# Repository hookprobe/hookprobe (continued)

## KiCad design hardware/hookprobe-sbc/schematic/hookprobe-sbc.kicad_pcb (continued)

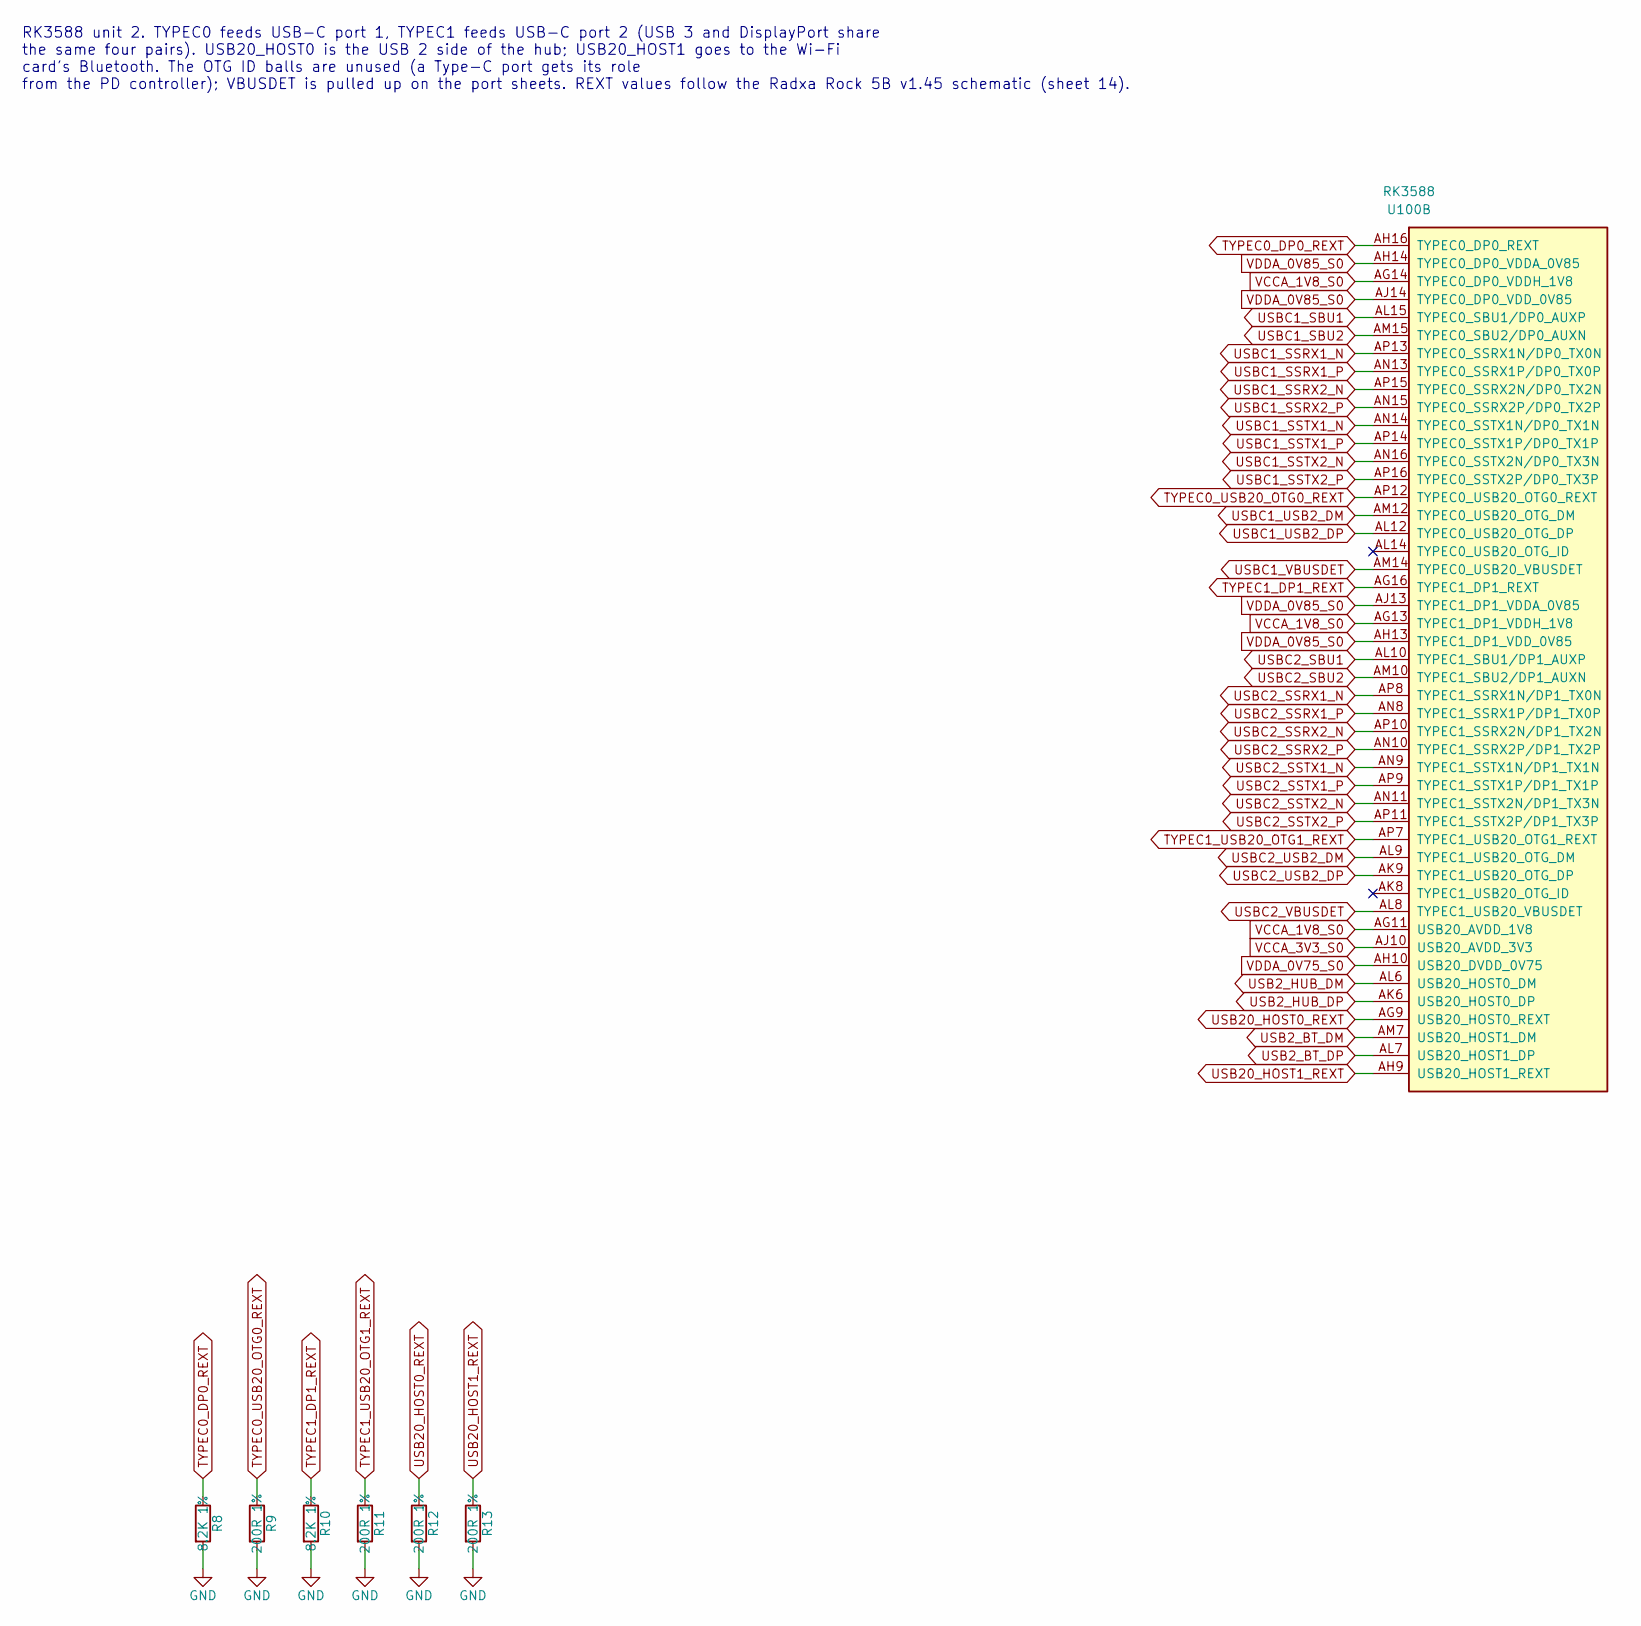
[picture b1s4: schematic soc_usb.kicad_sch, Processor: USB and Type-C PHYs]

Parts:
R8, R10: 8.2K 1%; R_0402_1005Metric
R9, R11, R12, R13: 200R 1%; R_0402_1005Metric
U100: RK3588; FCBGA-1088_L23.0-W23.0-P0.65-TL_RK3588

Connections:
GND: R8.2, R9.2, R10.2, R11.2, R12.2, R13.2; also elsewhere on the board
TYPEC0_DP0_REXT: R8.1, U100.AH16 (TYPEC0_DP0_REXT)
TYPEC0_USB20_OTG0_REXT: R9.1, U100.AP12 (TYPEC0_USB20_OTG0_REXT)
TYPEC1_DP1_REXT: R10.1, U100.AG16 (TYPEC1_DP1_REXT)
TYPEC1_USB20_OTG1_REXT: R11.1, U100.AP7 (TYPEC1_USB20_OTG1_REXT)
USB2_BT_DM: U100.AM7 (USB20_HOST1_DM); also elsewhere on the board
USB2_BT_DP: U100.AL7 (USB20_HOST1_DP); also elsewhere on the board
USB2_HUB_DM: U100.AL6 (USB20_HOST0_DM); also elsewhere on the board
USB2_HUB_DP: U100.AK6 (USB20_HOST0_DP); also elsewhere on the board
USB20_HOST0_REXT: R12.1, U100.AG9 (USB20_HOST0_REXT)
USB20_HOST1_REXT: R13.1, U100.AH9 (USB20_HOST1_REXT)
USBC1_SBU1: U100.AL15 (TYPEC0_SBU1/DP0_AUXP); also elsewhere on the board
USBC1_SBU2: U100.AM15 (TYPEC0_SBU2/DP0_AUXN); also elsewhere on the board
USBC1_SSRX1_N: U100.AP13 (TYPEC0_SSRX1N/DP0_TX0N); also elsewhere on the board
USBC1_SSRX1_P: U100.AN13 (TYPEC0_SSRX1P/DP0_TX0P); also elsewhere on the board
USBC1_SSRX2_N: U100.AP15 (TYPEC0_SSRX2N/DP0_TX2N); also elsewhere on the board
USBC1_SSRX2_P: U100.AN15 (TYPEC0_SSRX2P/DP0_TX2P); also elsewhere on the board
USBC1_SSTX1_N: U100.AN14 (TYPEC0_SSTX1N/DP0_TX1N); also elsewhere on the board
USBC1_SSTX1_P: U100.AP14 (TYPEC0_SSTX1P/DP0_TX1P); also elsewhere on the board
USBC1_SSTX2_N: U100.AN16 (TYPEC0_SSTX2N/DP0_TX3N); also elsewhere on the board
USBC1_SSTX2_P: U100.AP16 (TYPEC0_SSTX2P/DP0_TX3P); also elsewhere on the board
USBC1_USB2_DM: U100.AM12 (TYPEC0_USB20_OTG_DM); also elsewhere on the board
USBC1_USB2_DP: U100.AL12 (TYPEC0_USB20_OTG_DP); also elsewhere on the board
USBC1_VBUSDET: U100.AM14 (TYPEC0_USB20_VBUSDET); also elsewhere on the board
USBC2_SBU1: U100.AL10 (TYPEC1_SBU1/DP1_AUXP); also elsewhere on the board
USBC2_SBU2: U100.AM10 (TYPEC1_SBU2/DP1_AUXN); also elsewhere on the board
USBC2_SSRX1_N: U100.AP8 (TYPEC1_SSRX1N/DP1_TX0N); also elsewhere on the board
USBC2_SSRX1_P: U100.AN8 (TYPEC1_SSRX1P/DP1_TX0P); also elsewhere on the board
USBC2_SSRX2_N: U100.AP10 (TYPEC1_SSRX2N/DP1_TX2N); also elsewhere on the board
USBC2_SSRX2_P: U100.AN10 (TYPEC1_SSRX2P/DP1_TX2P); also elsewhere on the board
USBC2_SSTX1_N: U100.AN9 (TYPEC1_SSTX1N/DP1_TX1N); also elsewhere on the board
USBC2_SSTX1_P: U100.AP9 (TYPEC1_SSTX1P/DP1_TX1P); also elsewhere on the board
USBC2_SSTX2_N: U100.AN11 (TYPEC1_SSTX2N/DP1_TX3N); also elsewhere on the board
USBC2_SSTX2_P: U100.AP11 (TYPEC1_SSTX2P/DP1_TX3P); also elsewhere on the board
USBC2_USB2_DM: U100.AL9 (TYPEC1_USB20_OTG_DM); also elsewhere on the board
USBC2_USB2_DP: U100.AK9 (TYPEC1_USB20_OTG_DP); also elsewhere on the board
USBC2_VBUSDET: U100.AL8 (TYPEC1_USB20_VBUSDET); also elsewhere on the board
VCCA_1V8_S0: U100.AG11 (USB20_AVDD_1V8), U100.AG13 (TYPEC1_DP1_VDDH_1V8), U100.AG14 (TYPEC0_DP0_VDDH_1V8); also elsewhere on the board
VCCA_3V3_S0: U100.AJ10 (USB20_AVDD_3V3); also elsewhere on the board
VDDA_0V75_S0: U100.AH10 (USB20_DVDD_0V75); also elsewhere on the board
VDDA_0V85_S0: U100.AH13 (TYPEC1_DP1_VDD_0V85), U100.AH14 (TYPEC0_DP0_VDDA_0V85), U100.AJ13 (TYPEC1_DP1_VDDA_0V85), U100.AJ14 (TYPEC0_DP0_VDD_0V85); also elsewhere on the board

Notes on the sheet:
RK3588 unit 2. TYPEC0 feeds USB-C port 1, TYPEC1 feeds USB-C port 2 (USB 3 and DisplayPort share the same four pairs). USB20_HOST0 is the USB 2 side of the hub; USB20_HOST1 goes to the Wi-Fi card's Bluetooth. The OTG ID balls are unused (a Type-C port gets its role from the PD controller); VBUSDET 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

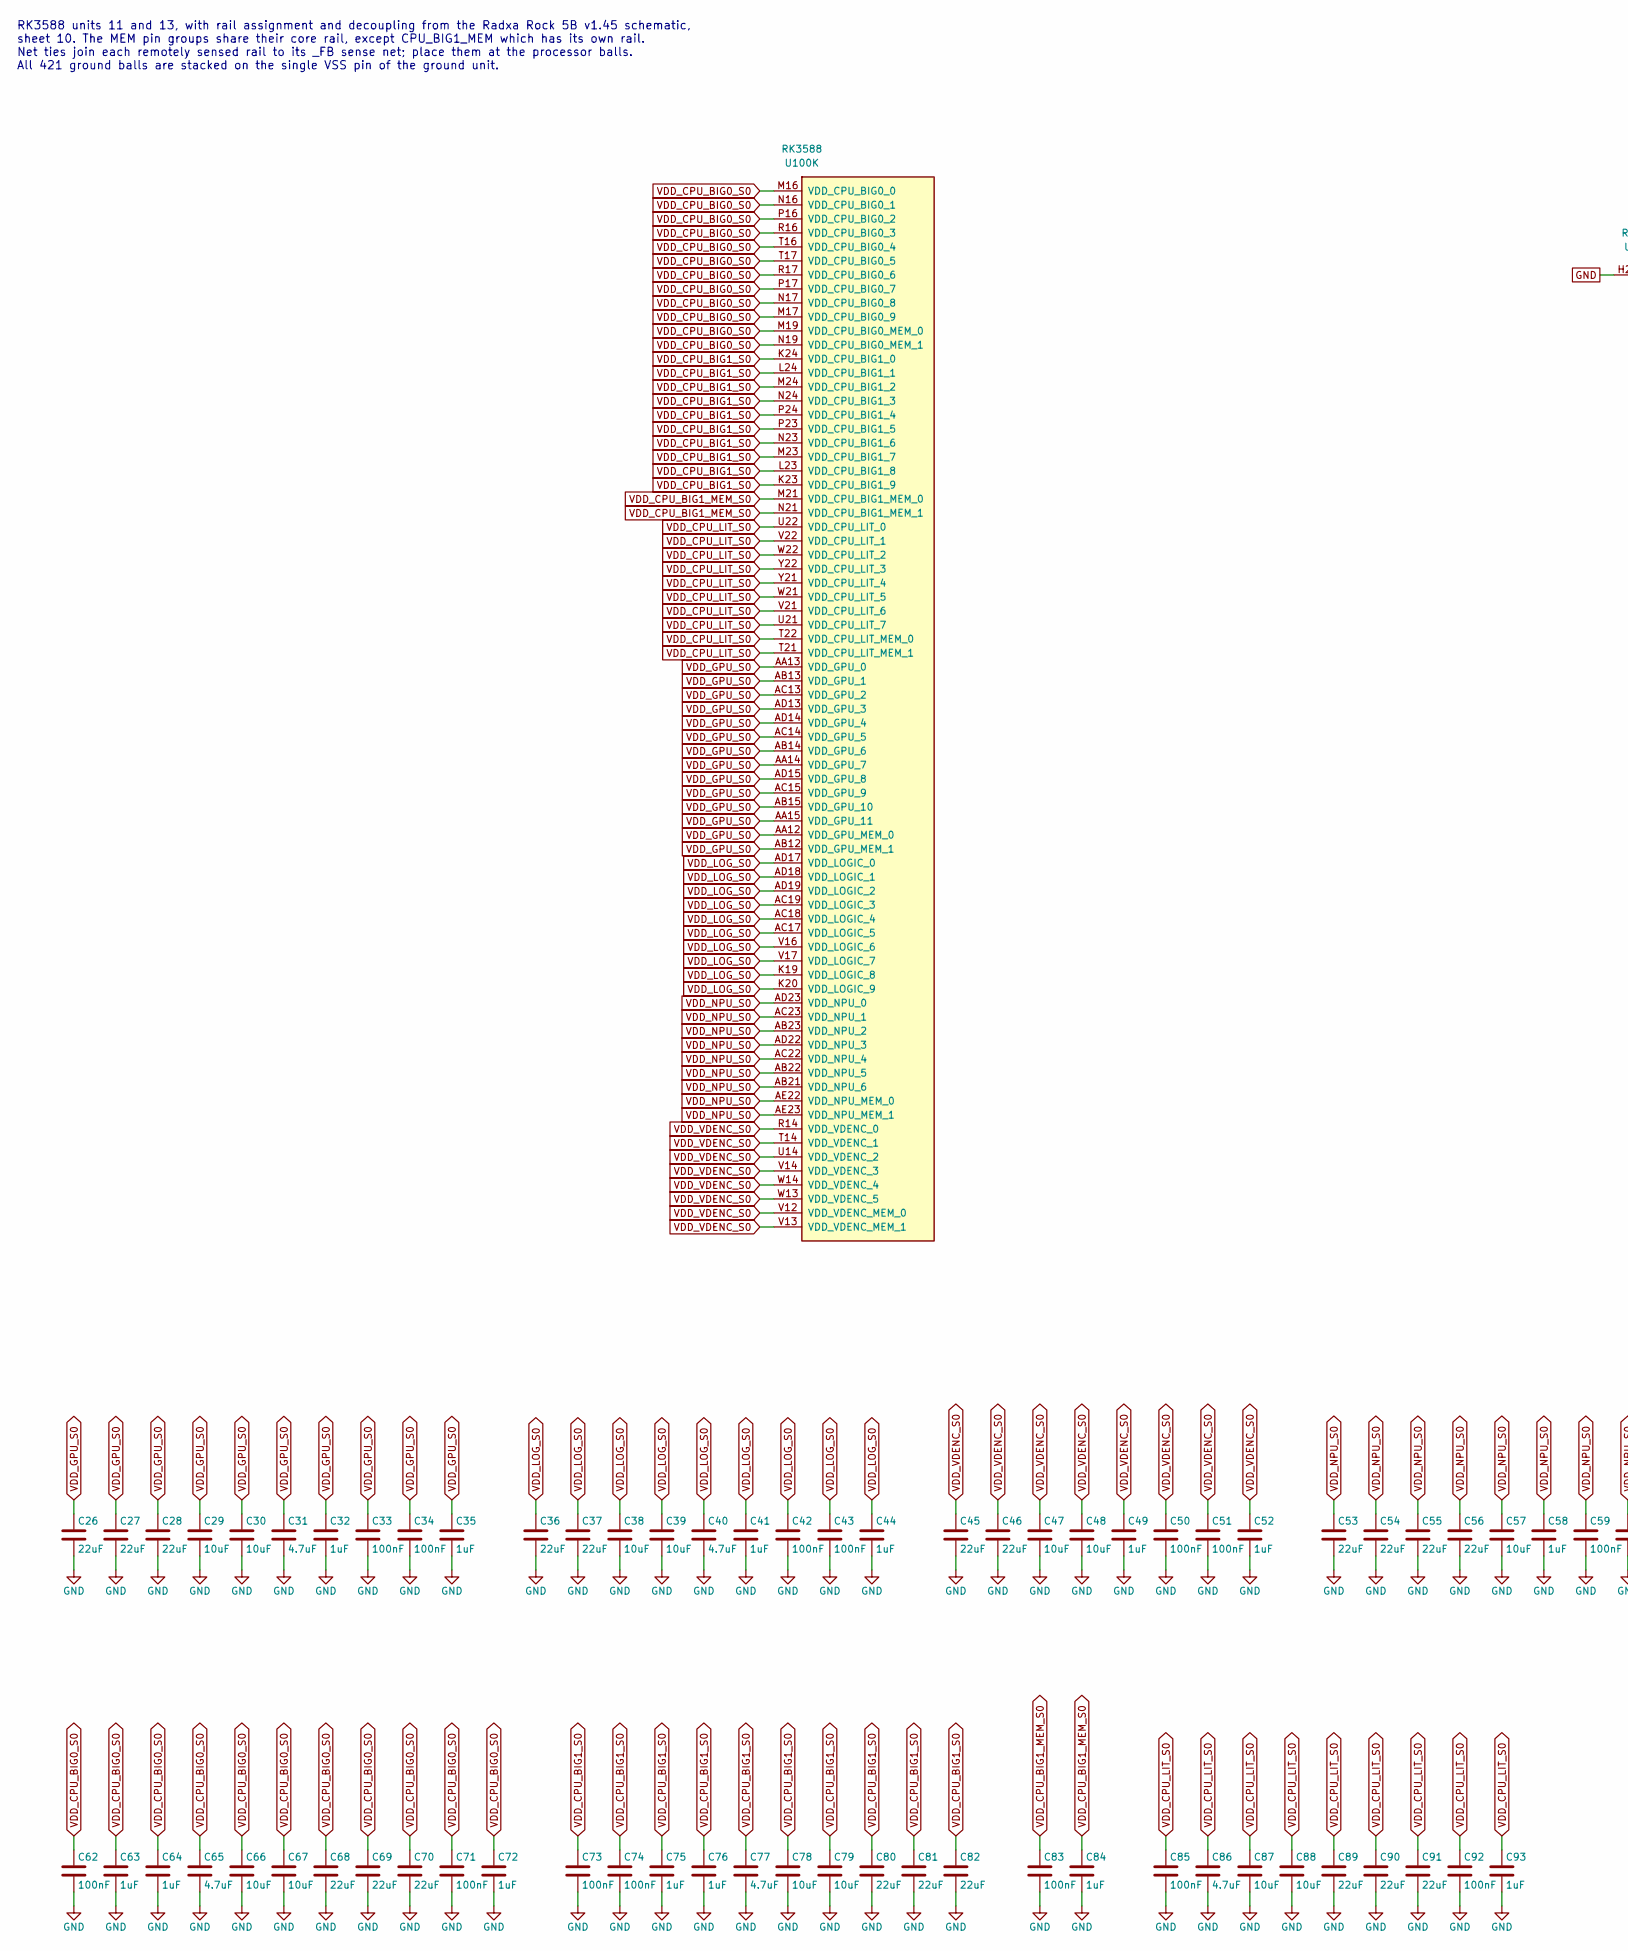
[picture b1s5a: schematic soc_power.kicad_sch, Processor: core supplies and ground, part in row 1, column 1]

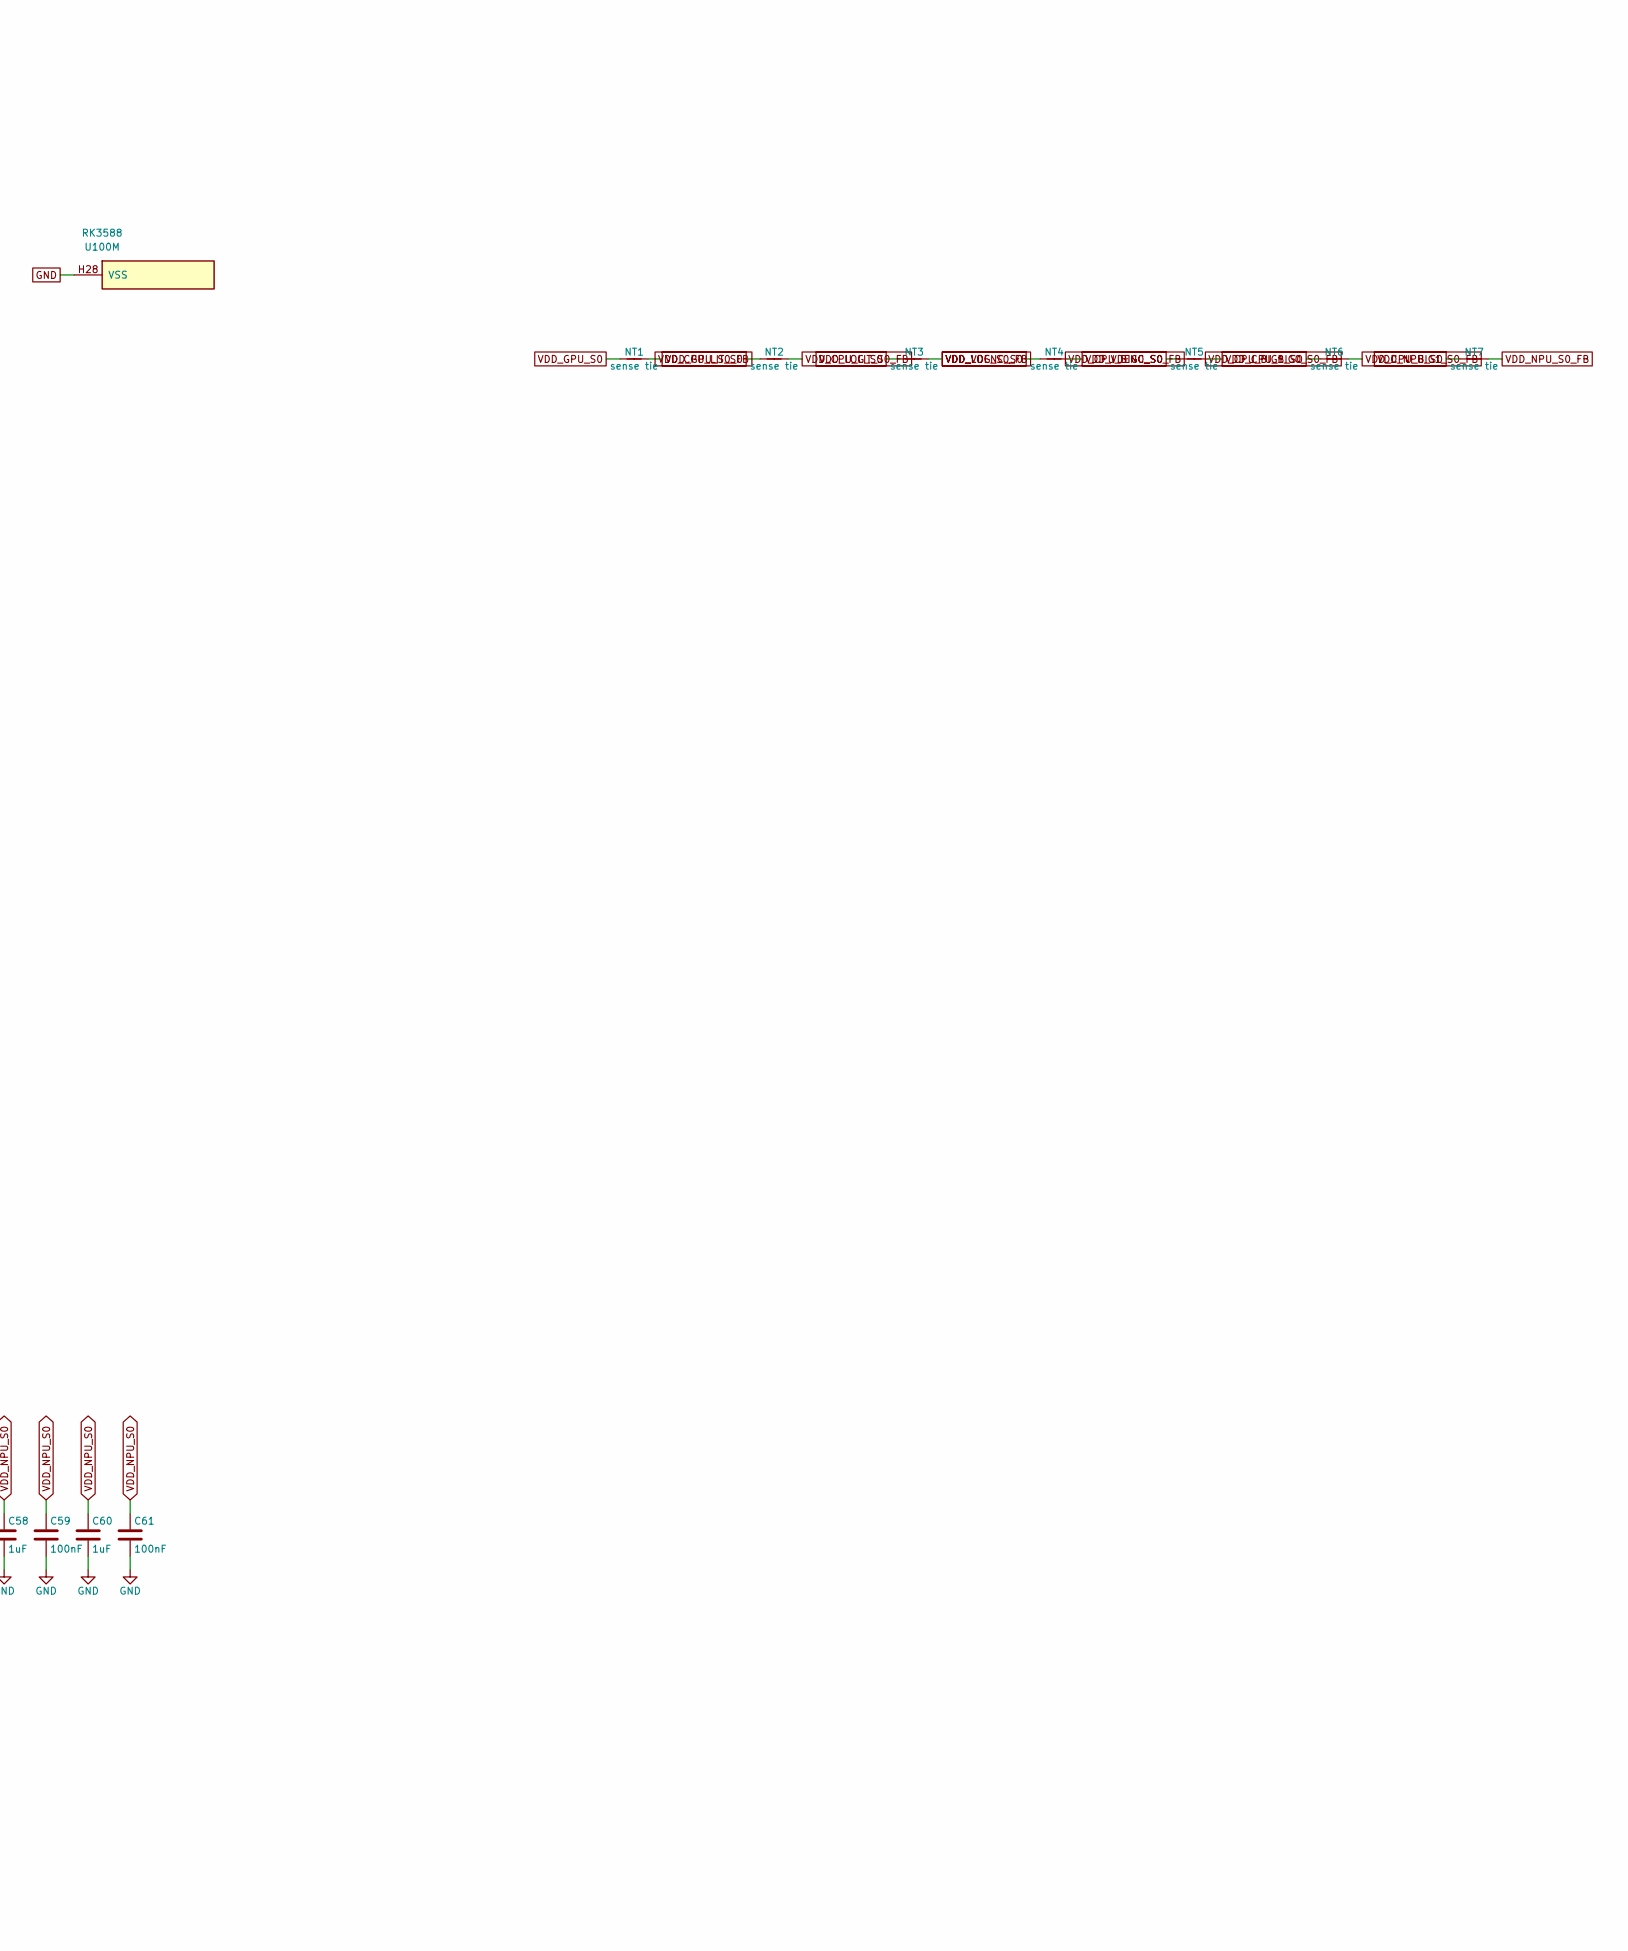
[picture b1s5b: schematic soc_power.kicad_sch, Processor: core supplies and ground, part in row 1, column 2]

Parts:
C26, C27, C28, C36, C37, C45, C46, C53, C54, C55, C56, C68, C69, C70, C80, C81, C82, C89, C90, C91: 22uF; C_0603_1608Metric
C29, C30, C38, C39, C47, C48, C57, C66, C67, C78, C79, C87, C88: 10uF; C_0402_1005Metric
C31, C40, C65, C77, C86: 4.7uF; C_0402_1005Metric
C32, C35, C41, C44, C49, C52, C58, C60, C63, C64, C72, C75, C76, C84, C93: 1uF; C_0402_1005Metric
C33, C34, C42, C43, C50, C51, C59, C61, C62, C71, C73, C74, C83, C85, C92: 100nF; C_0402_1005Metric
NT1, NT2, NT3, NT4, NT5, NT6, NT7: sense tie; NetTie-2_SMD_Pad0.5mm
U100: RK3588; FCBGA-1088_L23.0-W23.0-P0.65-TL_RK3588

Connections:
GND: C26.2, C27.2, C28.2, C29.2, C30.2, C31.2, C32.2, C33.2, C34.2, C35.2, C36.2, C37.2, C38.2, C39.2, C40.2, C41.2, C42.2, C43.2, C44.2, C45.2, C46.2, C47.2, C48.2, C49.2, C50.2, C51.2, C52.2, C53.2, C54.2, C55.2, C56.2, C57.2, C58.2, C59.2, C60.2, C61.2, C62.2, C63.2, C64.2, C65.2, C66.2, C67.2, C68.2, C69.2, C70.2, C71.2, C72.2, C73.2, C74.2, C75.2, C76.2, C77.2, C78.2, C79.2, C80.2, C81.2, C82.2, C83.2, C84.2, C85.2, C86.2, C87.2, C88.2, C89.2, C90.2, C91.2, C92.2, C93.2, U100.A1 (VSS), U100.A11 (VSS), U100.A14 (VSS), U100.A34 (VSS), U100.AA3 (VSS), U100.AA6 (VSS), U100.AA8 (VSS), U100.AA10 (VSS), U100.AA11 (VSS), U100.AA16 (VSS), U100.AA17 (VSS), U100.AA18 (VSS), U100.AA19 (VSS), U100.AA20 (VSS), U100.AA21 (VSS), U100.AA22 (VSS), U100.AA23 (VSS), U100.AA24 (VSS), U100.AA31 (VSS), U100.AB3 (VSS), U100.AB5 (VSS), U100.AB6 (VSS), U100.AB7 (VSS), U100.AB8 (VSS), U100.AB10 (VSS), U100.AB11 (VSS), U100.AB16 (VSS), U100.AB17 (VSS), U100.AB18 (VSS), U100.AB19 (VSS), U100.AB20 (VSS), U100.AB24 (VSS), U100.AB27 (VSS), U100.AB29 (VSS), U100.AB32 (VSS), U100.AC3 (VSS), U100.AC4 (VSS), U100.AC5 (VSS), U100.AC8 (VSS), U100.AC10 (VSS), U100.AC11 (VSS), U100.AC12 (VSS), U100.AC16 (VSS), U100.AC20 (VSS), U100.AC21 (VSS), U100.AC24 (VSS), U100.AC27 (VSS), U100.AD5 (VSS), U100.AD8 (VSS), U100.AD10 (VSS), U100.AD11 (VSS), U100.AD12 (VSS), U100.AD16 (VSS), U100.AD20 (VSS), U100.AD21 (VSS), U100.AD24 (VSS), U100.AD25 (VSS), U100.AD26 (VSS), U100.AE3 (VSS), U100.AE6 (VSS), U100.AE7 (VSS), U100.AE9 (VSS), U100.AE11 (VSS), U100.AE12 (VSS), U100.AE13 (VSS), U100.AE14 (VSS), U100.AE15 (VSS), U100.AE16 (VSS), U100.AE18 (VSS), U100.AE19 (VSS), U100.AE20 (VSS), U100.AE21 (VSS), U100.AE24 (VSS), U100.AE26 (VSS), U100.AF4 (VSS), U100.AF7 (VSS), U100.AF8 (VSS), U100.AF11 (VSS), U100.AF12 (VSS), U100.AF13 (VSS), U100.AF14 (VSS), U100.AF15 (VSS), U100.AF16 (VSS), U100.AF21 (VSS), U100.AF22 (VSS), U100.AF24 (VSS), U100.AF25 (VSS), U100.AF27 (VSS), U100.AF28 (VSS), U100.AF29 (VSS), U100.AF30 (VSS), U100.AF31 (VSS), U100.AF32 (VSS), U100.AG3 (VSS), U100.AG6 (VSS), U100.AG7 (VSS), U100.AG10 (VSS), U100.AG12 (VSS), U100.AG15 (VSS), U100.AG18 (VSS), U100.AG21 (VSS), U100.AG22 (VSS), U100.AG30 (VSS), U100.AH4 (VSS), U100.AH8 (VSS), U100.AH11 (VSS), U100.AH12 (VSS), U100.AH15 (VSS), U100.AH21 (VSS), U100.AH22 (VSS), U100.AH23 (VSS), U100.AJ3 (VSS), U100.AJ7 (VSS), U100.AJ8 (VSS), U100.AJ9 (VSS), U100.AJ11 (VSS), U100.AJ12 (VSS), U100.AJ15 (VSS), U100.AJ16 (VSS), U100.AJ18 (VSS), U100.AJ21 (VSS), U100.AJ22 (VSS), U100.AJ23 (VSS), U100.AJ30 (VSS), U100.AK4 (VSS), U100.AK5 (VSS), U100.AK7 (VSS), U100.AK10 (VSS), U100.AK11 (VSS), U100.AK12 (VSS), U100.AK13 (VSS), U100.AK14 (VSS), U100.AK23 (VSS), U100.AK28 (VSS), U100.AK29 (VSS), U100.AL3 (VSS), U100.AL4 (VSS), U100.AL5 (VSS), U100.AL11 (VSS), U100.AL13 (VSS), U100.AL23 (VSS), U100.AL25 (VSS), U100.AM4 (VSS), U100.AM8 (VSS), U100.AM9 (VSS), U100.AM18 (VSS), U100.AM20 (VSS), U100.AM22 (VSS), U100.AM23 (VSS), U100.AM24 (VSS), U100.AM26 (VSS), U100.AM28 (VSS), U100.AM30 (VSS), U100.AN7 (VSS), U100.AN12 (VSS), U100.AN23 (VSS), U100.AN31 (VSS), U100.AP1 (VSS), U100.AP17 (VSS), U100.AP23 (VSS), U100.AP34 (VSS), U100.B6 (VSS), U100.B19 (VSS), U100.B24 (VSS), U100.B27 (VSS), U100.B33 (VSS), U100.C3 (VSS), U100.C4 (VSS), U100.C5 (VSS), U100.C6 (VSS), U100.C7 (VSS), U100.C8 (VSS), U100.C9 (VSS), U100.C10 (VSS), U100.C11 (VSS), U100.C12 (VSS), U100.C13 (VSS), U100.C14 (VSS), U100.C15 (VSS), U100.C16 (VSS), U100.C17 (VSS), U100.C18 (VSS), U100.C20 (VSS), U100.C21 (VSS), U100.C22 (VSS), U100.C23 (VSS), U100.C26 (VSS), U100.C28 (VSS), U100.C30 (VSS), U100.C32 (VSS), U100.D3 (VSS), U100.D23 (VSS), U100.D24 (VSS), U100.D31 (VSS), U100.E3 (VSS), U100.E6 (VSS), U100.E8 (VSS), U100.E12 (VSS), U100.E18 (VSS), U100.E20 (VSS), U100.E22 (VSS), U100.E23 (VSS), U100.E32 (VSS), U100.F3 (VSS), U100.F7 (VSS), U100.F9 (VSS), U100.F10 (VSS), U100.F11 (VSS), U100.F13 (VSS), U100.F14 (VSS), U100.F15 (VSS), U100.F16 (VSS), U100.F19 (VSS), U100.F20 (VSS), U100.F21 (VSS), U100.F22 (VSS), U100.F23 (VSS), U100.F31 (VSS), U100.G3 (VSS), U100.G6 (VSS), U100.G10 (VSS), U100.G15 (VSS), U100.G19 (VSS), U100.G21 (VSS), U100.G22 (VSS), U100.G25 (VSS), U100.G32 (VSS), U100.H3 (VSS), U100.H6 (VSS), U100.H10 (VSS), U100.H12 (VSS), U100.H14 (VSS), U100.H19 (VSS), U100.H22 (VSS), U100.H25 (VSS), U100.H26 (VSS), U100.H28 (VSS), U100.H31 (VSS), U100.J3 (VSS), U100.J4 (VSS), U100.J5 (VSS), U100.J6 (VSS), U100.J10 (VSS), U100.J11 (VSS), U100.J12 (VSS), U100.J13 (VSS), U100.J14 (VSS), U100.J15 (VSS), U100.J16 (VSS), U100.J18 (VSS), U100.J19 (VSS), U100.J20 (VSS), U100.J21 (VSS), U100.J22 (VSS), U100.J23 (VSS), U100.J24 (VSS), U100.J25 (VSS), U100.J27 (VSS), U100.J28 (VSS), U100.J29 (VSS), U100.J32 (VSS), U100.K3 (VSS), U100.K6 (VSS), U100.K8 (VSS), U100.K9 (VSS), U100.K18 (VSS), U100.K21 (VSS), U100.K22 (VSS), U100.K26 (VSS), U100.K31 (VSS), U100.K32 (VSS), U100.L1 (VSS), U100.L3 (VSS), U100.L6 (VSS), U100.L9 (VSS), U100.L16 (VSS), U100.L19 (VSS), U100.L20 (VSS), U100.L21 (VSS), U100.L22 (VSS), U100.L25 (VSS), U100.L26 (VSS), U100.L31 (VSS), U100.M3 (VSS), U100.M6 (VSS), U100.M9 (VSS), U100.M11 (VSS), U100.M14 (VSS), U100.M15 (VSS), U100.M18 (VSS), U100.M20 (VSS), U100.M22 (VSS), U100.M25 (VSS), U100.M26 (VSS), U100.M32 (VSS), U100.N3 (VSS), U100.N6 (VSS), U100.N9 (VSS), U100.N11 (VSS), U100.N14 (VSS), U100.N15 (VSS), U100.N18 (VSS), U100.N20 (VSS), U100.N22 (VSS), U100.N25 (VSS), U100.N26 (VSS), U100.N29 (VSS), U100.N32 (VSS), U100.P1 (VSS), U100.P3 (VSS), U100.P6 (VSS), U100.P8 (VSS), U100.P9 (VSS), U100.P11 (VSS), U100.P14 (VSS), U100.P15 (VSS), U100.P18 (VSS), U100.P19 (VSS), U100.P20 (VSS), U100.P21 (VSS), U100.P22 (VSS), U100.P25 (VSS), U100.P26 (VSS), U100.P34 (VSS), U100.R3 (VSS), U100.R5 (VSS), U100.R8 (VSS), U100.R9 (VSS), U100.R11 (VSS), U100.R13 (VSS), U100.R15 (VSS), U100.R18 (VSS), U100.R19 (VSS), U100.R20 (VSS), U100.R21 (VSS), U100.R22 (VSS), U100.R23 (VSS), U100.R24 (VSS), U100.R25 (VSS), U100.R26 (VSS), U100.R28 (VSS), U100.R33 (VSS), U100.T3 (VSS), U100.T6 (VSS), U100.T9 (VSS), U100.T11 (VSS), U100.T13 (VSS), U100.T15 (VSS), U100.T18 (VSS), U100.T19 (VSS), U100.T20 (VSS), U100.T23 (VSS), U100.T24 (VSS), U100.T25 (VSS), U100.T26 (VSS), U100.T27 (VSS), U100.T33 (VSS), U100.U3 (VSS), U100.U12 (VSS), U100.U13 (VSS), U100.U15 (VSS), U100.U16 (VSS), U100.U17 (VSS), U100.U19 (VSS), U100.U20 (VSS), U100.U23 (VSS), U100.U24 (VSS), U100.U30 (VSS), U100.U31 (VSS), U100.U34 (VSS), U100.V3 (VSS), U100.V4 (VSS), U100.V5 (VSS), U100.V8 (VSS), U100.V9 (VSS), U100.V10 (VSS), U100.V11 (VSS), U100.V15 (VSS), U100.V18 (VSS), U100.V19 (VSS), U100.V23 (VSS), U100.V24 (VSS), U100.V25 (VSS), U100.V27 (VSS), U100.V30 (VSS), U100.W2 (VSS), U100.W3 (VSS), U100.W6 (VSS), U100.W7 (VSS), U100.W9 (VSS), U100.W10 (VSS), U100.W11 (VSS), U100.W12 (VSS), U100.W15 (VSS), U100.W16 (VSS), U100.W17 (VSS), U100.W18 (VSS), U100.W19 (VSS), U100.W20 (VSS), U100.W23 (VSS), U100.W24 (VSS), U100.W27 (VSS), U100.Y3 (VSS), U100.Y5 (VSS), U100.Y6 (VSS), U100.Y8 (VSS), U100.Y9 (VSS), U100.Y10 (VSS), U100.Y11 (VSS), U100.Y12 (VSS), U100.Y13 (VSS), U100.Y14 (VSS), U100.Y15 (VSS), U100.Y16 (VSS), U100.Y17 (VSS), U100.Y18 (VSS), U100.Y19 (VSS), U100.Y20 (VSS), U100.Y23 (VSS), U100.Y24 (VSS), U100.Y28 (VSS); also elsewhere on the board
VDD_CPU_BIG0_S0: C62.1, C63.1, C64.1, C65.1, C66.1, C67.1, C68.1, C69.1, C70.1, C71.1, C72.1, NT5.1, U100.M16 (VDD_CPU_BIG0_0), U100.M17 (VDD_CPU_BIG0_9), U100.M19 (VDD_CPU_BIG0_MEM_0), U100.N16 (VDD_CPU_BIG0_1), U100.N17 (VDD_CPU_BIG0_8), U100.N19 (VDD_CPU_BIG0_MEM_1), U100.P16 (VDD_CPU_BIG0_2), U100.P17 (VDD_CPU_BIG0_7), U100.R16 (VDD_CPU_BIG0_3), U100.R17 (VDD_CPU_BIG0_6), U100.T16 (VDD_CPU_BIG0_4), U100.T17 (VDD_CPU_BIG0_5); also elsewhere on the board
VDD_CPU_BIG0_S0_FB: NT5.2; also elsewhere on the board
VDD_CPU_BIG1_MEM_S0: C83.1, C84.1, U100.M21 (VDD_CPU_BIG1_MEM_0), U100.N21 (VDD_CPU_BIG1_MEM_1); also elsewhere on the board
VDD_CPU_BIG1_S0: C73.1, C74.1, C75.1, C76.1, C77.1, C78.1, C79.1, C80.1, C81.1, C82.1, NT6.1, U100.K23 (VDD_CPU_BIG1_9), U100.K24 (VDD_CPU_BIG1_0), U100.L23 (VDD_CPU_BIG1_8), U100.L24 (VDD_CPU_BIG1_1), U100.M23 (VDD_CPU_BIG1_7), U100.M24 (VDD_CPU_BIG1_2), U100.N23 (VDD_CPU_BIG1_6), U100.N24 (VDD_CPU_BIG1_3), U100.P23 (VDD_CPU_BIG1_5), U100.P24 (VDD_CPU_BIG1_4); also elsewhere on the board
VDD_CPU_BIG1_S0_FB: NT6.2; also elsewhere on the board
VDD_CPU_LIT_S0: C85.1, C86.1, C87.1, C88.1, C89.1, C90.1, C91.1, C92.1, C93.1, NT2.1, U100.T21 (VDD_CPU_LIT_MEM_1), U100.T22 (VDD_CPU_LIT_MEM_0), U100.U21 (VDD_CPU_LIT_7), U100.U22 (VDD_CPU_LIT_0), U100.V21 (VDD_CPU_LIT_6), U100.V22 (VDD_CPU_LIT_1), U100.W21 (VDD_CPU_LIT_5), U100.W22 (VDD_CPU_LIT_2), U100.Y21 (VDD_CPU_LIT_4), U100.Y22 (VDD_CPU_LIT_3); also elsewhere on the board
VDD_CPU_LIT_S0_FB: NT2.2; also elsewhere on the board
VDD_GPU_S0: C26.1, C27.1, C28.1, C29.1, C30.1, C31.1, C32.1, C33.1, C34.1, C35.1, NT1.1, U100.AA12 (VDD_GPU_MEM_0), U100.AA13 (VDD_GPU_0), U100.AA14 (VDD_GPU_7), U100.AA15 (VDD_GPU_11), U100.AB12 (VDD_GPU_MEM_1), U100.AB13 (VDD_GPU_1), U100.AB14 (VDD_GPU_6), U100.AB15 (VDD_GPU_10), U100.AC13 (VDD_GPU_2), U100.AC14 (VDD_GPU_5), U100.AC15 (VDD_GPU_9), U100.AD13 (VDD_GPU_3), U100.AD14 (VDD_GPU_4), U100.AD15 (VDD_GPU_8); also elsewhere on the board
VDD_GPU_S0_FB: NT1.2; also elsewhere on the board
VDD_LOG_S0: C36.1, C37.1, C38.1, C39.1, C40.1, C41.1, C42.1, C43.1, C44.1, NT3.1, U100.AC17 (VDD_LOGIC_5), U100.AC18 (VDD_LOGIC_4), U100.AC19 (VDD_LOGIC_3), U100.AD17 (VDD_LOGIC_0), U100.AD18 (VDD_LOGIC_1), U100.AD19 (VDD_LOGIC_2), U100.K19 (VDD_LOGIC_8), U100.K20 (VDD_LOGIC_9), U100.V16 (VDD_LOGIC_6), U100.V17 (VDD_LOGIC_7); also elsewhere on the board
VDD_LOG_S0_FB: NT3.2; also elsewhere on the board
VDD_NPU_S0: C53.1, C54.1, C55.1, C56.1, C57.1, C58.1, C59.1, C60.1, C61.1, NT7.1, U100.AB21 (VDD_NPU_6), U100.AB22 (VDD_NPU_5), U100.AB23 (VDD_NPU_2), U100.AC22 (VDD_NPU_4), U100.AC23 (VDD_NPU_1), U100.AD22 (VDD_NPU_3), U100.AD23 (VDD_NPU_0), U100.AE22 (VDD_NPU_MEM_0), U100.AE23 (VDD_NPU_MEM_1); also elsewhere on the board
VDD_NPU_S0_FB: NT7.2; also elsewhere on the board
VDD_VDENC_S0: C45.1, C46.1, C47.1, C48.1, C49.1, C50.1, C51.1, C52.1, NT4.1, U100.R14 (VDD_VDENC_0), U100.T14 (VDD_VDENC_1), U100.U14 (VDD_VDENC_2), U100.V12 (VDD_VDENC_MEM_0), U100.V13 (VDD_VDENC_MEM_1), U100.V14 (VDD_VDENC_3), U100.W13 (VDD_VDENC_5), U100.W14 (VDD_VDENC_4); also elsewhere on the board
VDD_VDENC_S0_FB: NT4.2; also elsewhere on the board

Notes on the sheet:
RK3588 units 11 and 13, with rail assignment and decoupling from the Radxa Rock 5B v1.45 schematic, sheet 10. The MEM pin groups share their core rail, except CPU_BIG1_MEM which has its own rail. Net ties join each remotely sensed rail to its _FB sense net; place them at the processor balls. All 42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

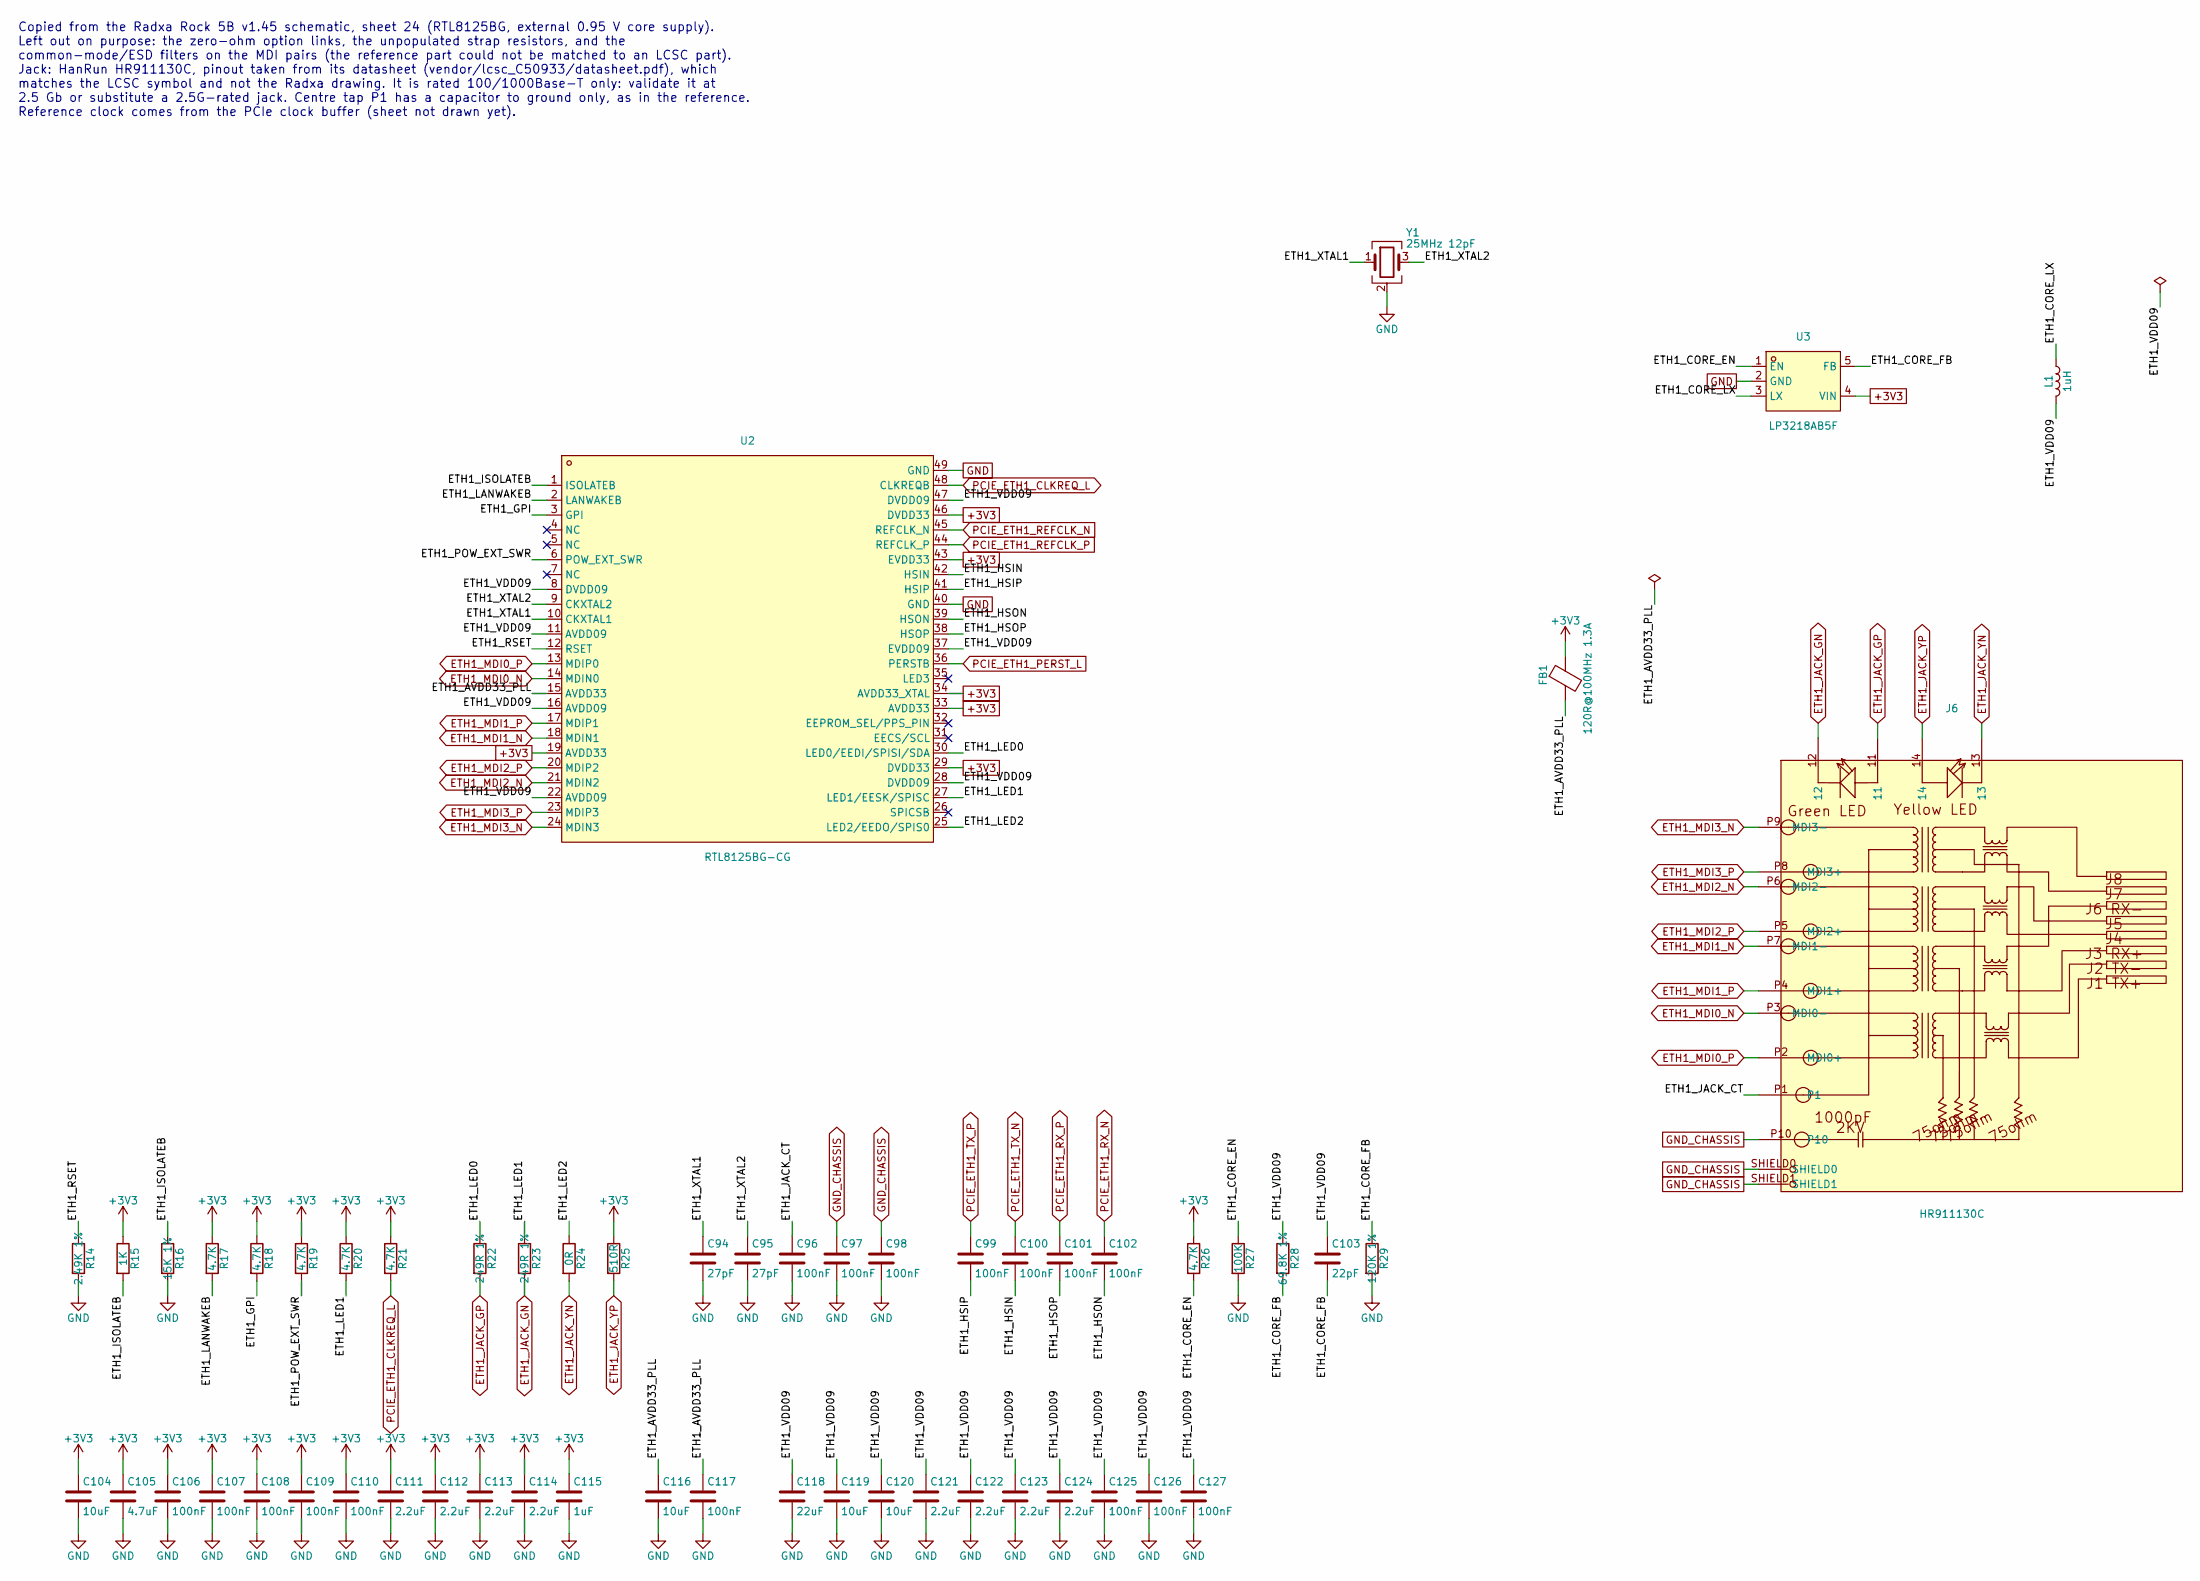
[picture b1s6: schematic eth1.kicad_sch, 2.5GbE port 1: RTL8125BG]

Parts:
C94, C95: 27pF; C_0402_1005Metric
C96, C97, C98, C99, C100, C101, C102, C106, C107, C108, C109, C110, C117, C125, C126, C127: 100nF; C_0402_1005Metric
C103: 22pF; C_0402_1005Metric
C104, C116, C119, C120: 10uF; C_0805_2012Metric
C105: 4.7uF; C_0805_2012Metric
C111, C112, C113, C114, C121, C122, C123, C124: 2.2uF; C_0402_1005Metric
C115: 1uF; C_0402_1005Metric
C118: 22uF; C_0805_2012Metric
FB1: 120R@100MHz 1.3A; L_0402_1005Metric; Part UPZ1005D121-1R3TF
J6: HR911130C; RJ45-TH_HR911130C; LCSC C50933
L1: 1uH; L_0805_2012Metric
R14: 2.49K 1%; R_0402_1005Metric
R15: 1K; R_0402_1005Metric
R16: 15K 1%; R_0402_1005Metric
R17, R18, R19, R20, R21, R26: 4.7K; R_0402_1005Metric
R22, R23: 249R 1%; R_0402_1005Metric
R24: 0R; R_0402_1005Metric
R25: 510R; R_0402_1005Metric
R27: 100K; R_0402_1005Metric
R28: 69.8K 1%; R_0402_1005Metric
R29: 120K 1%; R_0402_1005Metric
U2: RTL8125BG-CG; TQFN-48_L6.0-W6.0-P0.40-BL-EP4.5; LCSC C3013605
U3: LP3218AB5F; SOT-23-5_L2.9-W1.6-P0.95-LS2.8-BR; LCSC C517210
Y1: 25MHz 12pF; Crystal_SMD_3225-4Pin_3.2x2.5mm

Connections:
+3V3: C104.1, C105.1, C106.1, C107.1, C108.1, C109.1, C110.1, C111.1, C112.1, C113.1, C114.1, C115.1, FB1.1, R15.1, R17.1, R18.1, R19.1, R20.1, R21.1, R25.1, R26.1, U2.19 (AVDD33), U2.29 (DVDD33), U2.33 (AVDD33), U2.34 (AVDD33_XTAL), U2.43 (EVDD33), U2.46 (DVDD33), U3.4 (VIN); also elsewhere on the board
/2.5GbE port 1: RTL8125BG/ETH1_AVDD33_PLL: C116.1, C117.1, FB1.2, U2.15 (AVDD33)
/2.5GbE port 1: RTL8125BG/ETH1_CORE_EN: R26.2, R27.1, U3.1 (EN)
/2.5GbE port 1: RTL8125BG/ETH1_CORE_FB: C103.2, R28.2, R29.1, U3.5 (FB)
/2.5GbE port 1: RTL8125BG/ETH1_CORE_LX: L1.1, U3.3 (LX)
/2.5GbE port 1: RTL8125BG/ETH1_GPI: R18.2, U2.3 (GPI)
/2.5GbE port 1: RTL8125BG/ETH1_HSIN: C100.2, U2.42 (HSIN)
/2.5GbE port 1: RTL8125BG/ETH1_HSIP: C99.2, U2.41 (HSIP)
/2.5GbE port 1: RTL8125BG/ETH1_HSON: C102.2, U2.39 (HSON)
/2.5GbE port 1: RTL8125BG/ETH1_HSOP: C101.2, U2.38 (HSOP)
/2.5GbE port 1: RTL8125BG/ETH1_ISOLATEB: R15.2, R16.1, U2.1 (ISOLATEB)
/2.5GbE port 1: RTL8125BG/ETH1_JACK_CT: C96.1, J6.P1
/2.5GbE port 1: RTL8125BG/ETH1_LANWAKEB: R17.2, U2.2 (LANWAKEB)
/2.5GbE port 1: RTL8125BG/ETH1_LED0: R22.1, U2.30 (LED0/EEDI/SPISI/SDA)
/2.5GbE port 1: RTL8125BG/ETH1_LED1: R20.2, R23.1, U2.27 (LED1/EESK/SPISC)
/2.5GbE port 1: RTL8125BG/ETH1_LED2: R24.1, U2.25 (LED2/EEDO/SPIS0)
/2.5GbE port 1: RTL8125BG/ETH1_POW_EXT_SWR: R19.2, U2.6 (POW_EXT_SWR)
/2.5GbE port 1: RTL8125BG/ETH1_RSET: R14.1, U2.12 (RSET)
/2.5GbE port 1: RTL8125BG/ETH1_VDD09: C103.1, C118.1, C119.1, C120.1, C121.1, C122.1, C123.1, C124.1, C125.1, C126.1, C127.1, L1.2, R28.1, U2.8 (DVDD09), U2.11 (AVDD09), U2.16 (AVDD09), U2.22 (AVDD09), U2.28 (DVDD09), U2.37 (EVDD09), U2.47 (DVDD09)
/2.5GbE port 1: RTL8125BG/ETH1_XTAL1: C94.1, U2.10 (CKXTAL1), Y1.1
/2.5GbE port 1: RTL8125BG/ETH1_XTAL2: C95.1, U2.9 (CKXTAL2), Y1.3
ETH1_JACK_GN: J6.12, R23.2
ETH1_JACK_GP: J6.11, R22.2
ETH1_JACK_YN: J6.13, R24.2
ETH1_JACK_YP: J6.14, R25.2
ETH1_MDI0_N: J6.P3 (MDI0-), U2.14 (MDIN0)
ETH1_MDI0_P: J6.P2 (MDI0+), U2.13 (MDIP0)
ETH1_MDI1_N: J6.P7 (MDI1-), U2.18 (MDIN1)
ETH1_MDI1_P: J6.P4 (MDI1+), U2.17 (MDIP1)
ETH1_MDI2_N: J6.P6 (MDI2-), U2.21 (MDIN2)
ETH1_MDI2_P: J6.P5 (MDI2+), U2.20 (MDIP2)
ETH1_MDI3_N: J6.P9 (MDI3-), U2.24 (MDIN3)
ETH1_MDI3_P: J6.P8 (MDI3+), U2.23 (MDIP3)
GND: C94.2, C95.2, C96.2, C97.2, C98.2, C104.2, C105.2, C106.2, C107.2, C108.2, C109.2, C110.2, C111.2, C112.2, C113.2, C114.2, C115.2, C116.2, C117.2, C118.2, C119.2, C120.2, C121.2, C122.2, C123.2, C124.2, C125.2, C126.2, C127.2, R14.2, R16.2, R27.2, R29.2, U2.40 (GND), U2.49 (GND), U3.2 (GND), Y1.2 (G), Y1.4 (G); also elsewhere on the board
GND_CHASSIS: C97.1, C98.1, J6.P10, J6.SHIELD0, J6.SHIELD1; also elsewhere on the board
PCIE_ETH1_CLKREQ_L: R21.2, U2.48 (CLKREQB); also elsewhere on the board
PCIE_ETH1_PERST_L: U2.36 (PERSTB); also elsewhere on the board
PCIE_ETH1_REFCLK_N: U2.45 (REFCLK_N); also elsewhere on the board
PCIE_ETH1_REFCLK_P: U2.44 (REFCLK_P); also elsewhere on the board
PCIE_ETH1_RX_N: C102.1; also elsewhere on the board
PCIE_ETH1_RX_P: C101.1; also elsewhere on the board
PCIE_ETH1_TX_N: C100.1; also elsewhere on the board
PCIE_ETH1_TX_P: C99.1; also elsewhere on the board

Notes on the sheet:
Copied from the Radxa Rock 5B v1.45 schematic, sheet 24 (RTL8125BG, external 0.95 V core supply). Left out on purpose: the zero-ohm option links, the unpopulated strap resistors, and the common-mode/ESD filters on the MDI pairs (the reference part could not be matched to an LCSC part). Jack: HanRun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
